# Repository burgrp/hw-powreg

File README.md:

# hw-powreg
Modular PWM regulator

Line switch study: https://tinyurl.com/2k9l2ror

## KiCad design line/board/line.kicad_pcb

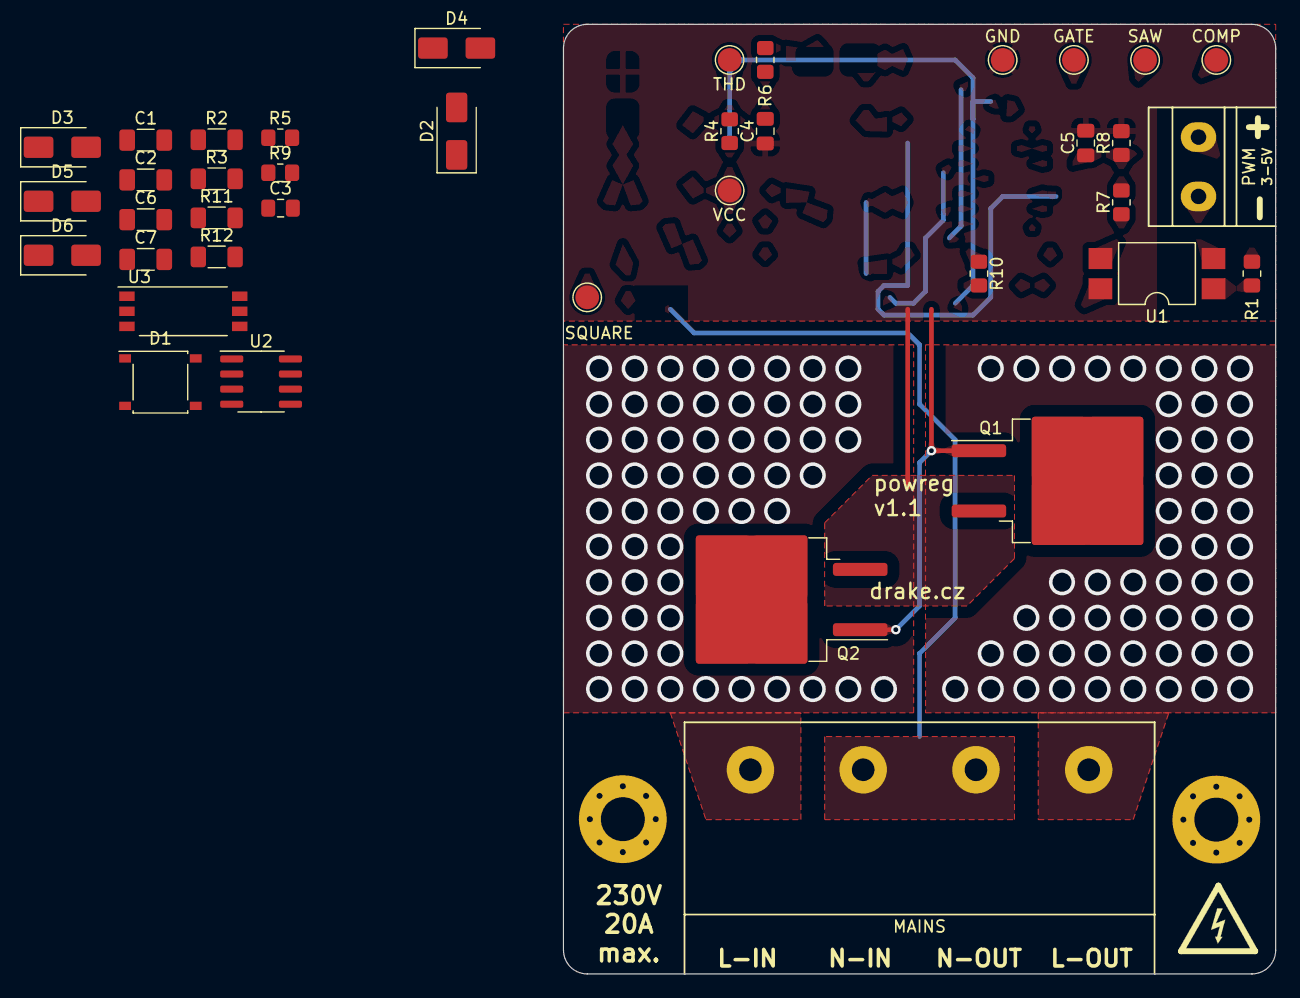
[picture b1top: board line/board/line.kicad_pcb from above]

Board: 2 copper layers, 60.0 x 80.0 mm, 41 parts (0 on the bottom side), 22 nets.

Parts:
C1, C2, C6, C7: 10u/50V; C_1206_3216Metric_Pad1.33x1.80mm_HandSolder
C3, C4, C5: 100n; C_0805_2012Metric_Pad1.18x1.45mm_HandSolder
D1: AB10S-DC; Diode_Bridge_Diotec_ABS
D2, D5: 1SMA4747A; D_SMA
D3, D4: SS13A; D_SMA
D6: ES1D; D_SMA
H1, H2: MountingHole; MountingHole_3.7mm_Pad_Via
J1: PWM; DG301-5.0-02
J2: MAINS; HB-9500-4P
Q1, Q2: WMM38N60C2; TO-263-2
R1, R9: 270R; R_0805_2012Metric_Pad1.20x1.40mm_HandSolder
R2, R3, R11, R12: 100k (250mW min.); R_1206_3216Metric_Pad1.30x1.75mm_HandSolder
R4: 1M; R_0805_2012Metric_Pad1.20x1.40mm_HandSolder
R5, R6: 220k; R_0805_2012Metric_Pad1.20x1.40mm_HandSolder
R7, R8: 100k; R_0805_2012Metric_Pad1.20x1.40mm_HandSolder
R10: 3R9; R_0805_2012Metric_Pad1.20x1.40mm_HandSolder
TP1: SQUARE; TestPoint_Pad_D2.0mm
TP2: THD; TestPoint_Pad_D2.0mm
TP3: VCC; TestPoint_Pad_D2.0mm
TP4: GND; TestPoint_Pad_D2.0mm
TP5: SAW; TestPoint_Pad_D2.0mm
TP6: COMP; TestPoint_Pad_D2.0mm
TP7: GATE; TestPoint_Pad_D2.0mm
U1: LTV-817S; SMDIP-4_W9.53mm
U2: LM358; SOIC-8_3.9x4.9mm_P1.27mm
U3: TLP2345; SO-6L_10x3.84mm_P1.27mm

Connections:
/MAINS_L_IN: J2.1, Q1.2 (D), R2.2, R3.2
/MAINS_L_OUT: J2.4, Q2.2 (D)
/MAINS_N: D1.3, J2.2, J2.3, R11.1, R12.1
GND: C1.2, C2.2, C3.2, C4.2, C5.2, D1.2 (-), D2.2 (A), R5.1, R8.1, TP4.1, U2.4 (V-), U3.3 (K)
unnamed: D1.1 (+), D2.1 (K), D3.2 (A), TP1.1, U2.3 (+)
unnamed: D1.4, R2.1, R3.1
unnamed: C4.1, D4.2 (A), R6.2, TP5.1, U2.6 (-)
unnamed: D4.1 (K), R6.1, U2.1
unnamed: C6.1, C7.1, D5.2 (A), Q1.3 (S), Q2.3 (S), U3.4 (GND)
unnamed: C6.2, C7.2, D5.1 (K), D6.1 (K), U3.6 (VDD)
unnamed: D6.2 (A), R11.2, R12.2
unnamed: J1.1, U1.2
unnamed: J1.2, R1.1
unnamed: Q1.1 (G), Q2.1 (G), R10.2
unnamed: R1.2, U1.1
unnamed: R7.2, U1.3
unnamed: R9.1, TP7.1, U2.7
unnamed: R4.1, R5.2, TP2.1, U2.2 (-)
unnamed: C5.1, R7.1, R8.2, TP6.1, U2.5 (+)
unnamed: R9.2, U3.1 (A)
unnamed: R10.1, U3.5 (VO)
VCC: C1.1, C2.1, C3.1, D3.1 (K), R4.2, TP3.1, U1.4, U2.8 (V+)

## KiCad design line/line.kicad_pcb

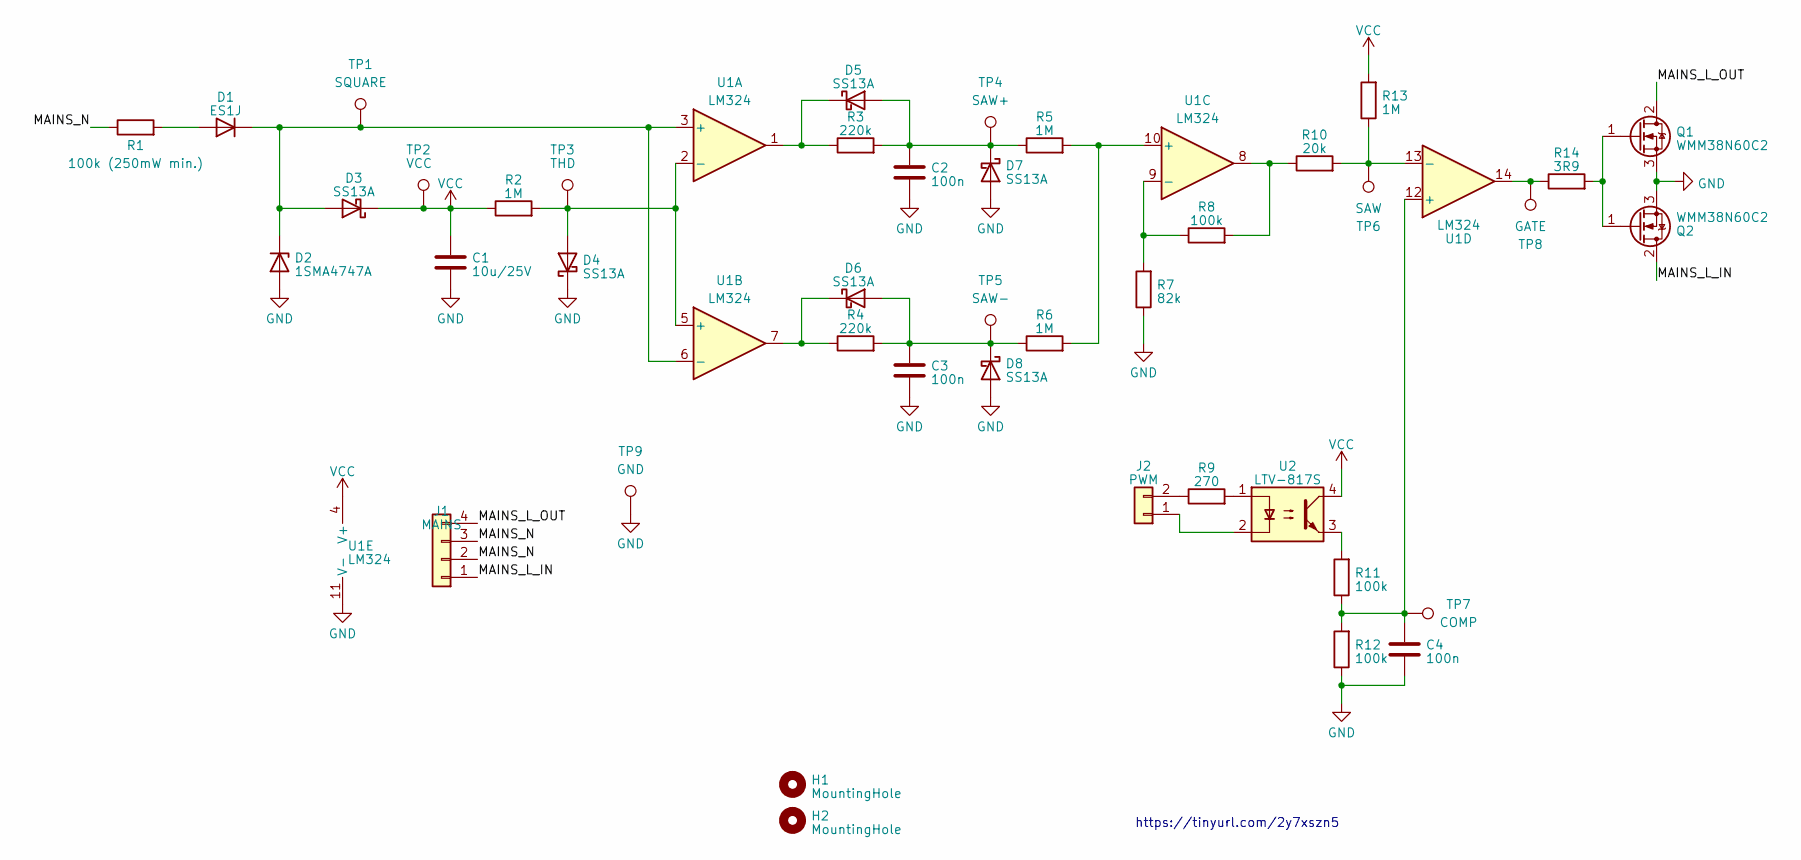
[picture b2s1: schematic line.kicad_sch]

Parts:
C1: 10u/25V; C_0805_2012Metric_Pad1.18x1.45mm_HandSolder
C2, C3, C4: 100n; C_0805_2012Metric_Pad1.18x1.45mm_HandSolder
D1: ES1J; D_SMA_Handsoldering
D2: 1SMA4747A; D_SMA_Handsoldering
D3, D4, D5, D6, D7, D8: SS13A; D_SMA_Handsoldering
H1, H2: MountingHole; MountingHole_3.7mm_Pad_Via
J1: MAINS; HB-9500-4P
J2: PWM; DG301-5.0-02
Q1, Q2: WMM38N60C2; TO-263-2
R1: 100k (250mW min.); R_1206_3216Metric_Pad1.30x1.75mm_HandSolder
R2, R5, R6, R13: 1M; R_0805_2012Metric_Pad1.20x1.40mm_HandSolder
R3, R4: 220k; R_0805_2012Metric_Pad1.20x1.40mm_HandSolder
R7: 82k; R_0805_2012Metric_Pad1.20x1.40mm_HandSolder
R8, R11, R12: 100k; R_0805_2012Metric_Pad1.20x1.40mm_HandSolder
R9: 270; R_0805_2012Metric_Pad1.20x1.40mm_HandSolder
R10: 20k; R_0805_2012Metric_Pad1.20x1.40mm_HandSolder
R14: 3R9; R_0805_2012Metric_Pad1.20x1.40mm_HandSolder
TP1: SQUARE; TestPoint_Pad_D2.0mm
TP2: VCC; TestPoint_Pad_D2.0mm
TP3: THD; TestPoint_Pad_D2.0mm
TP4: SAW+; TestPoint_Pad_D2.0mm
TP5: SAW-; TestPoint_Pad_D2.0mm
TP6: SAW; TestPoint_Pad_D2.0mm
TP7: COMP; TestPoint_Pad_D2.0mm
TP8: GATE; TestPoint_Pad_D2.0mm
TP9: GND; TestPoint_Pad_D2.0mm
U1: LM324; SOIC-14_3.9x8.7mm_P1.27mm
U2: LTV-817S; SMDIP-4_W9.53mm

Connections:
/MAINS_L_IN: J1.1, Q2.2 (D)
/MAINS_L_OUT: J1.4, Q1.2 (D)
/MAINS_N: J1.2, J1.3, R1.1
GND: C1.2, C2.2, C3.2, C4.2, D2.2 (A), D4.1 (K), D7.2 (A), D8.2 (A), Q1.3 (S), Q2.3 (S), R7.1, R12.1, TP9.1, U1.11 (V-)
unnamed: D1.2 (A), R1.2
unnamed: D1.1 (K), D2.1 (K), D3.2 (A), TP1.1, U1.3 (+), U1.6 (-)
unnamed: D4.2 (A), R2.2, TP3.1, U1.2 (-), U1.5 (+)
unnamed: C2.1, D5.2 (A), D7.1 (K), R3.2, R5.1, TP4.1
unnamed: D5.1 (K), R3.1, U1.1
unnamed: C3.1, D6.2 (A), D8.1 (K), R4.2, R6.1, TP5.1
unnamed: D6.1 (K), R4.1, U1.7
unnamed: J2.1, U2.2
unnamed: J2.2, R9.1
unnamed: Q1.1 (G), Q2.1 (G), R14.2
unnamed: R9.2, U2.1
unnamed: R8.2, R10.1, U1.8
unnamed: R11.2, U2.3
unnamed: R14.1, TP8.1, U1.14
unnamed: R5.2, R6.2, U1.10 (+)
unnamed: R7.2, R8.1, U1.9 (-)
unnamed: C4.1, R11.1, R12.2, TP7.1, U1.12 (+)
unnamed: R10.2, R13.1, TP6.1, U1.13 (-)
VCC: C1.1, D3.1 (K), R2.1, R13.2, TP2.1, U1.4 (V+), U2.4

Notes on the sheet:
https://tinyurl.com/2y7xszn5

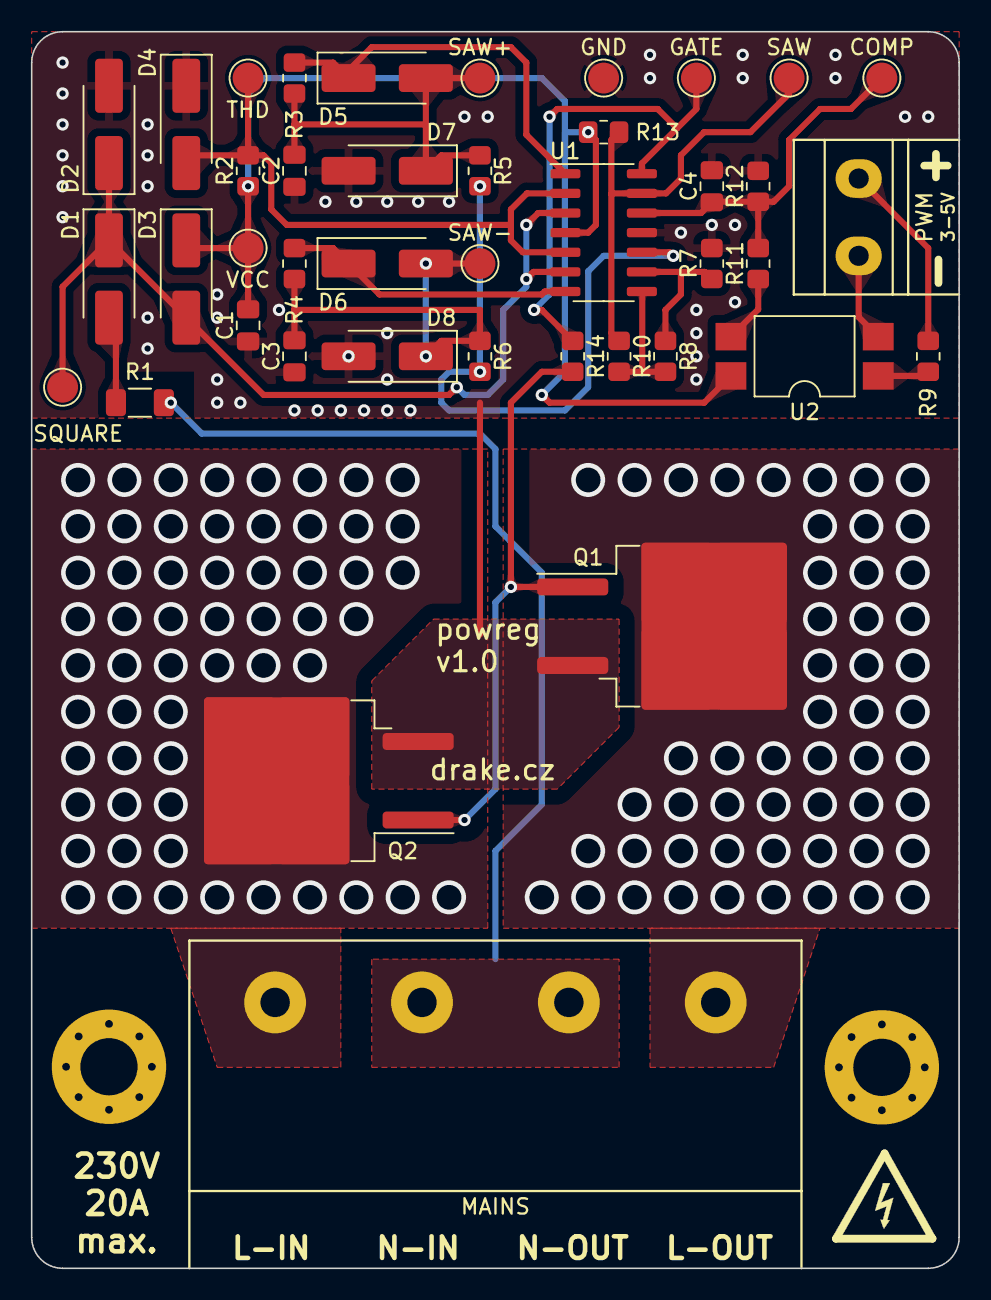
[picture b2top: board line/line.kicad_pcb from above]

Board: 2 copper layers, 60.0 x 80.0 mm, 43 parts (0 on the bottom side), 23 nets.

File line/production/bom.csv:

Designator,Footprint,Quantity,Value,LCSC Part #
C1,0805,1,10u/25V,
C2,0805,1,100n,
C3,0805,1,100n,
C4,0805,1,100n,
D1,D_SMA_Handsoldering,1,BYG10J (J/K/M/Y),
D2,D_SMA_Handsoldering,1,SMAZ20-13-F,
"D3, D4, D5, D6, D7, D8",D_SMA_Handsoldering,6,SS13A,
"H1, H2",MountingHole_3.7mm_Pad_Via,2,MountingHole,
J1,HB-9500-4P,1,MAINS,
J2,DG301-5.0-02,1,PWM,
"Q1, Q2",TO-263-2,2,WMM38N60C2,
R1,1206,1,100k (250mW min.),
R10,0805,1,20k,
R11,0805,1,100k,
R12,0805,1,100k,
R13,0805,1,1M,
R14,0805,1,3R9,
R2,0805,1,1M,
R3,0805,1,220k,
R4,0805,1,220k,
R5,0805,1,1M,
R6,0805,1,1M,
R7,0805,1,82k,
R8,0805,1,100k,
R9,0805,1,270,
TP1,TestPoint_Pad_D2.0mm,1,SQUARE,
TP2,TestPoint_Pad_D2.0mm,1,VCC,
TP3,TestPoint_Pad_D2.0mm,1,THD,
TP4,TestPoint_Pad_D2.0mm,1,SAW+,
TP5,TestPoint_Pad_D2.0mm,1,SAW-,
TP6,TestPoint_Pad_D2.0mm,1,SAW,
TP7,TestPoint_Pad_D2.0mm,1,COMP,
TP8,TestPoint_Pad_D2.0mm,1,GATE,
TP9,TestPoint_Pad_D2.0mm,1,GND,
U1,SOIC-14_3.9x8.7mm_P1.27mm,1,LM324,
U2,SMDIP-4_W9.53mm,1,LTV-817S,

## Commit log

2023-06-04 blink
2023-06-08 write_reg16, read_reg16 operations in cpu.zig
